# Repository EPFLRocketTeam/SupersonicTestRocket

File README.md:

# SupersonicTestRocket
Repository for the avionics going on the supersonic test rocket.
This contains the various files and folders required to get a Teensy 3.5 working with the code for data acquisition as well as the necessary post-processing scripts.

# Usage
1.  Flash the firmware onto the Teensy 3.5.  
  a. If no modifications are required to the code, this can be done by taking the file ```firmware.hex``` and flashing it directly with the Teensy flasher.  
  b. If modifications are required, Platform.io will need to be installed on the local computer on VSCode. Instructions can be found [here](https://platformio.org/platformio-ide). The required modifications can then be made and ```main.cpp``` can be recompiled using the IDE.
2.  Log data on the Teensy 3.5.  
  a. Logging should start automatically when powered on.  
  b. If it is not, press and hold button 1 for 1 second. The green LED (LED1 on the PCB) should then light up for 1 second. If the button is released during this window, logging should start indicated by the green LED staying on continuously.
3.  Stop logging on the Teensy 3.5 (optional but highly recommended!).  
  a. Logging needs to be stopped in the software using the following button sequence:  
  b. Hold button 1 for 3 seconds. The green LED should turn off and the red LED should turn on for 1 second.  
  c. Let go of all buttons for 5 seconds. After this, the red LED should turn on again for 1 second.  
  d. Hold button 2 for 7 seconds. After this, the red LED should turn on again for 1 second. Let go of the button.  
  e. Logging should now stop, indicated by no LEDs turned on. Logging can be resumed again following the instructions from step 2.  
  f. If logging is not manually stopped, there could be filesystem corruption with a power loss to the Teensy.
4.  Put the Teensy in MTP mode to transfer data to a local computer.  
  a. Flash ```mtp.ino``` onto the Teensy 3.5 using the Arduino IDE.  
  b. The SD card should appear on the computer as a normal device. transfer the most recent files.
5.  Decode the binary files using the MATLAB binary decoder.  
  a. Put the recently acquired files in the ```inFiles``` folder of the MATLAB decoder.  
  b. run the decoder ```decoder.m``` using MATLAB.  
  c. The files should now be in ```outFiles```.
6.  Run the Kalman filter on the files (not yet implemented!).  
  a. Transfer the contents of ```outFiles``` to the relevant folder of the Kalman filter.  
  b. Run the Kalman filter.  

# Contents
```
SupersonicTestRocket
|   README.md
|
│───archives            archived code
│───bin_decoder         MATLAB binary decoder for raw output files
|   |   decoder.m       the decoder itself
|   |
|   |───errorFiles      input files that had errors during processing
|   |───inFiles         input files to process by the decoder
|   |───outFiles        .csv files generated by the decoder
|   └───processedFiles  input files after successful processing
|
│───data_logger_supersonic_rocket   logger to put on the Teensy 3.5
|   |───.pio
|   |   └───build
|   |        └───teensy35
|   |           |   firmware.hex    the firmware to flash on the Teensy 3.5
|   |
|   └───src
│       │   main.cpp    the file that should be compiled with Platform.io
|
│───datasheets          datasheets for the sensors used on the rocket
│───KF                  MATLAB Kalman filter to process flight data
|   └───2D              2D simulations of the flight and KF testing
|   └───3D              the full 3D Kalman filter for flight data
|
|───mtp                 
|   └───mtp.ino         the code to run with the Arduino IDE to access the SD
|
└───PCB                 the Kicad files to reproduce the PCB
└───readings            interesting readings relevant to the project

```

# Collaborators
Joshua Cayetano-Emond

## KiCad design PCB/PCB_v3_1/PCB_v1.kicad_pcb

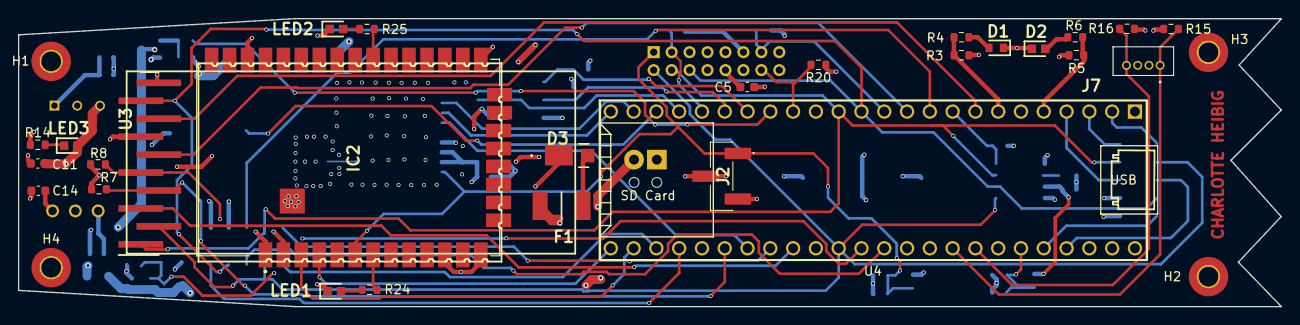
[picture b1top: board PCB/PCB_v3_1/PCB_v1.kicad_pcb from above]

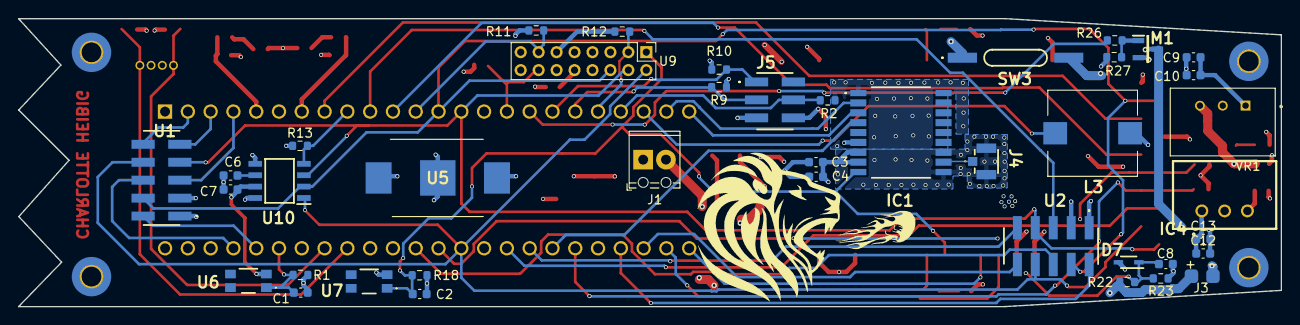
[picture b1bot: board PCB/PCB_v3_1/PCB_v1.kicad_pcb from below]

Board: 4 copper layers, 140.8 x 32.1 mm, 72 parts (41 on the bottom side), 57 nets.

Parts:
C1, C2, C3, C5, C10, C11, C13, C14: 100nF; C_0603_1608Metric
C4, C9, C12: 10uF; C_0603_1608Metric
C6: 1uF +/- 10% 10V; C_0603_1608Metric
C7: 100nF +/- 10% 10V; C_0603_1608Metric
C8: 1uF; C_0603_1608Metric
D1: White LED; LEDC1608X45N
D2: Red LED; LEDC1608X80N
D3: D_Schottky; V8PAN50M3I
D7: BZX584C3V3-G3-08; SOD2513X110N
F1: MINIASMDC150F_12-2; MINISMDC050F2
H1, H2, H3, H4: Board_Hole; MountingHole_2.2mm_M2_Pad_TopBottom
IC1: MAX-7C-0; MAX7C0
IC2: XB8X-DMUS-001; XBP9XDMRS001
IC4: TSR_0.5-2433; TSR-0.5-2433
J1: Altimax Power; TerminalBlock_Phoenix_MPT-0,5-2-2.54_1x02_P2.54mm_Horizontal
J2: 0878980304
J3: LiPo Connection; pad2
J4: CONUFL001-SMD-T; CONUFL001-SMD
J5: 57202G5203LF
J7: 1734598-4; 17345984
L3: SMI-1027-T-5V-R; SMI1027T5VR
LED1, LED2, LED3: 150060GS75000; LEDC1608X80N
M1: MNMOS; SOT95P237X112-3N
R1, R4, R6, R11, R12, R13, R20: 10kΩ; R_0603_1608Metric
R2, R9, R10, R15, R16, R18: 10k; R_0603_1608Metric
R3: 100Ω; R_0603_1608Metric
R5: 24Ω; R_0603_1608Metric
R7, R8, R27: 10kOhm; R_0603_1608Metric
R14: 10K; R_0603_1608Metric
R22, R23: ?; R_0603_1608Metric
R24, R25: 24; R_0603_1608Metric
R26: R; R_0603_1608Metric
SW3: MISM7R610
U1, U2: 57202G5205LF
U3: 1-2842102-0; HUSRSP10W50P200_2000X200X550P
U4: Teensy3.5; Teensy35_36_exterior_pins_only
U5: 3030
U6, U7: switch; RKC2SJF170SMTRLFS
U9: ADIS16470; PinHeader_2x08_P2.00mm_Vertical
U10: AIS1120SXTR; SOIC127P600X175-8N
VR1: TSR1-2450; CONV_TSR1-2450

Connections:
+3V3: C2.1, C3.1, C4.1, C5.1, C7.1, C14.1, IC1.7 (VCC_IO), IC1.8 (VCC), IC2.2 (VCC), IC4.3 (+VOUT), J5.6, R7.1, R8.1, R12.1, R13.1, R15.2, R16.2, R18.1, U1.3, U2.3, U3.7, U6.3, U9.10 (VDD), U9.11 (VDD), U9.12 (VDD), U10.7 (VDD)
+5V: C11.1, C12.1, C13.1, IC4.1 (+VIN), J7.3, LED3.2, U4.53 (Vin), VR1.3 (+VOUT)
/MISO0: U1.7, U2.7, U3.1, U4.14 (12_MISO0), U9.4 (DOUT), U10.3 (SDO)
/MOSI0: U1.4, U2.4, U3.9, U4.13 (11_MOSI0), U9.6 (DIN), U10.2 (SDI)
/RTC_supply: IC1.6 (V_BCKP), J2.2, U5.1, U5.3
/SCK0: U1.8, U2.8, U3.2, U4.40 (13_SCK0_LED), U9.2 (SCLK), U10.1 (SCL)
/aux1: J5.3, R9.2, U4.19 (27_RX1_SCK0)
/aux2: J5.1, R10.2, U4.18 (26_TX1_SCL2)
/aux3: J5.4, R2.1, U4.21 (29_PWM_CAN0TX_Touch)
/bat_voltage: C8.2, D7.1, R22.2, R23.1, U4.41 (14_A0_PWM_SCK0)
/button1: C1.1, R1.1, U4.48 (21_A7_PWM_CS0_MOSI1), U6.1
/buzzer_input: L3.1, U4.22 (30_PWM_CAN0RX_Touch)
/cs_acc: R13.2, U4.9 (7_RX3_MOSI0_SCL0), U10.4 (CS)
/cs_adis: R12.2, U4.20 (28_MOSI0), U9.3 (CS)
/cs_pressure_adc_1: U1.2, U4.49 (22_A8_PWM_Touch)
/cs_pressure_adc_2: U2.2, U4.33 (36_A17_PWM)
/cs_pressure_ee_1: U1.5, U4.4 (2_PWM)
/cs_pressure_ee_2: U2.5, U4.10 (8_TX3_MISO0_SDA0)
/cs_tc1: U1.9, U4.3 (1_TX1_MISO1_Touch)
/cs_tc2: U1.10, U4.2 (0_RX1_MOSI1_Touch)
/cs_tc3: U2.9, U4.37 (A21_DAC0)
/cs_tc4: U2.10, U4.32 (35_A16_PWM)
/dr_adis: R11.2, U4.12 (10_PWM_TX2_CS0), U9.13 (DR)
/dr_pressure_1: U1.6, U4.50 (23_A9_PWM_Touch)
/dr_pressure_2: U2.6, U4.42 (15_A1_CS0_Touch)
/enable_gnd: R26.1, U4.17 (25)
/gp0_spi: U3.3, U4.38 (A22_DAC1)
/gp3_spi: U3.8, U4.8 (6_PWM)
/gp4_spi: U3.6, U4.11 (9_PWM_RX2_CS0)
/led1: R3.2, R4.1, U4.7 (5_PWM_TX1_MISO1)
/led2: R5.1, R6.2, U4.5 (3_PWM_CAN0TX_SCL2)
/load_minus: J7.1, R15.1, U4.45 (18_A4_SDA0_Touch)
/load_plus: J7.4, R16.1, U4.46 (19_A5_SCL0_Touch)
/nReset: C2.2, IC1.9 (RESET_N), IC2.6 (~RESET), J2.1, R18.2, U7.1, U9.1 (RST)
/rx_ublox: IC1.3 (RXD), U4.24 (32_A13_TX4_SCK1)
/rx_xbee: IC2.4 (DIN/DIO14/~CONFIG), U4.30 (33_A14_TX5_CAN1TX_SCL0)
/scl_i2c: R8.2, U3.5, U4.34 (37_A18_PWM_SCL1)
/sda_i2c: R7.2, U3.4, U4.35 (38_A19_PWM_SDA1)
/sync_adis: R20.2, U4.16 (24), U9.14 (SYNC)
/timepulse_ublox: IC1.4 (TIMEPULSE), U4.36 (39_A20)
/tx_ublox: IC1.2 (TXD), U4.23 (31_A12_RX4_CS1)
/tx_xbee: IC2.3 (DIO13/DOUT), U4.31 (34_A15_RX5_CAN1RX_SDA0)
GND: C1.2, C3.2, C4.2, C5.2, C6.2, C7.2, C8.1, C9.2, C10.2, C11.2, C12.2, C13.2, C14.2, D1.1 (K), D2.1 (K), D7.2, H1.1, H2.1, H3.1, H4.1, IC1.1 (GND_1), IC1.10 (GND_2), IC1.12 (GND_3), IC2.1 (GND_1), IC2.11 (GND_2), IC2.13 (GND_3), IC2.22 (GND_4), IC2.35 (GND_5), IC2.38 (GND_6), IC4.2 (GND), J2.3, J4.2 (GND_1), J4.3 (GND_2), J5.5, J7.2, L3.2, LED1.1, LED2.1, M1.2 (S), R1.2, R2.2, R4.2, R6.1, R9.1, R10.1, R11.1, R14.2, R20.1, R23.2, R27.2, SW3.1 (A), U1.1, U2.1, U3.10, U4.1 (GND), U4.39 (GND), U5.2, U7.3, U9.7 (GND), U9.8 (GND), U9.9 (GND), U10.5 (GND), U10.8 (MP), VR1.2 (GND)
unnamed: C6.1, U10.6 (VREG)
unnamed: C9.1, C10.1, D3.1 (K), VR1.1 (+VIN)
unnamed: D1.2 (A), R3.1
unnamed: D2.2 (A), R5.2
unnamed: D3.2 (A), F1.2
unnamed: F1.1, J1.2, J3.2, R22.1
unnamed: IC1.11 (RF_IN), J4.1 (SIG)
unnamed: IC2.7 (DIO10/RSSI/PWM0), R24.1
unnamed: IC2.28 (DIO5/ASSOC), R25.2
unnamed: J1.1, J3.1, M1.1 (D), SW3.2 (B)
unnamed: LED1.2, R24.2
unnamed: LED2.2, R25.1
unnamed: LED3.1, R14.1
unnamed: M1.3 (G), R26.2, R27.1

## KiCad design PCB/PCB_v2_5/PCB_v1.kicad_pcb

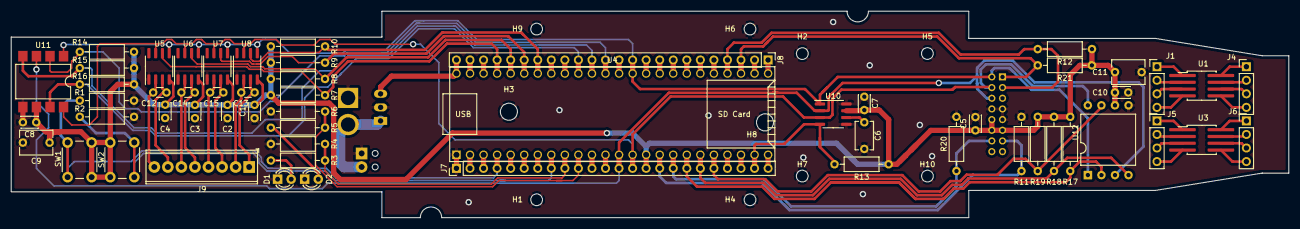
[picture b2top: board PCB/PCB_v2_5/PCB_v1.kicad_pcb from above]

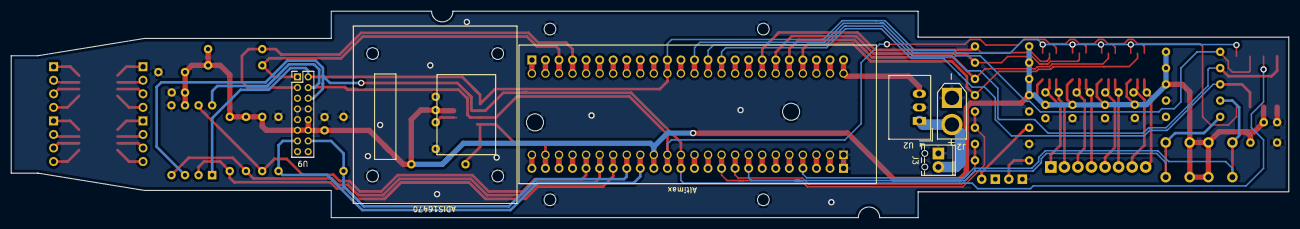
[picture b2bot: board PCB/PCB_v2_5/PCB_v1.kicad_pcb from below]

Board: 2 copper layers, 239.5 x 38.7 mm, 73 parts (6 on the bottom side), 76 nets.

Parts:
ADIS16470: ADIS16470
Altimax: AltimaxG4
C1, C2, C3, C4, C5, C8, C10: 0.1uF; C_Disc_D3.0mm_W2.0mm_P2.50mm
C6: 1uF +/- 10% 10V; C_Disc_D5.1mm_W3.2mm_P5.00mm
C7: 0.1uF +/- 10% 10V; C_Disc_D3.0mm_W2.0mm_P2.50mm
C9, C11: 10uF; C_Disc_D6.0mm_W4.4mm_P5.00mm
C12, C13, C14, C15: 10nF; C_Disc_D3.0mm_W1.6mm_P2.50mm
D1, D2: LED; LED_D3.0mm
H1, H4, H6, H9: Board_Hole; MountingHole_2.2mm_M2
H2, H5, H7, H10: IMU_hole; MountingHole_2.2mm_M2
H3, H8: Altimax_hole; MountingHole_3.2mm_M3
J1, J4, J5, J6: DIP; PinHeader_1x04_P2.54mm_Vertical
J2: XT30 Connector; AMASS_XT30U-F_1x02_P5.0mm_Vertical
J3: Altimax Power; TerminalBlock_Phoenix_MPT-0,5-2-2.54_1x02_P2.54mm_Horizontal
J7, J8: Conn_01x24_Male; PinHeader_1x24_P2.54mm_Vertical
J9: Thermocouples; TerminalBlock_Phoenix_MPT-0,5-8-2.54_1x08_P2.54mm_Horizontal
R1, R2, R4, R6, R7, R8, R9, R10, R11, R12, R13, R14, R15, R16, R17, R18, R19, R20, R21: 10kΩ; R_Axial_DIN0207_L6.3mm_D2.5mm_P10.16mm_Horizontal
R3, R5: 100Ω; R_Axial_DIN0207_L6.3mm_D2.5mm_P10.16mm_Horizontal
SW1, SW2: SW_Push; SW_PUSH_6mm
U1, U3: SOIC-8_Adapter; SOIC-8_3_to_8mm_P1.27mm
U2: TSR_1-2450; Converter_DCDC_TRACO_TSR-1_THT
U4: Teensy3.5; Teensy35_36_exterior_pins_only
U5, U6, U7, U8: MAX31855KASA; SOIC-8_3.9x4.9mm_P1.27mm
U9: ADIS16470; PinHeader_2x08_P2.00mm_Vertical
U10: AIS1120SXTR; SOIC-8_3.9x4.9mm_P1.27mm
U11: RSCMRNE015PASE3; SMDIP-8_W9.53mm
U12: RSCDJNI060PASE3; DIP-8_W13.08mm

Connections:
+3V3: C1.2, C2.2, C3.2, C4.2, C5.1, C7.1, C8.1, C9.1, C10.1, C11.1, J7.15, R7.2, R8.2, R9.2, R10.2, R12.1, R13.1, R14.2, R15.2, R16.2, R17.2, R18.2, R19.2, R21.1, SW1.2, SW2.1, U4.15, U5.4, U6.4, U7.4, U8.4, U9.10, U9.11, U9.12, U10.7, U11.6, U12.6
+5V: J8.24, U2.3, U4.53
/I/O/Button1: J7.4, R1.1, SW1.1, U4.4
/I/O/Button2: J7.8, R2.2, SW2.2, U4.8
/I/O/LED1: J7.9, R3.2, R4.1, U4.9
/I/O/LED2: J7.10, R5.1, R6.2, U4.10
/INS/CS_ADIS16470: J8.4, R12.2, U4.33, U9.3
/INS/CS_AIS1120: J7.23, R13.2, U4.23, U10.4
/INS/DR_ADIS16470: J7.16, R11.2, U4.16, U9.13
/INS/RST_ADIS16470: J8.3, R21.2, U4.32, U9.1
/INS/SYNC_ADIS16470: J7.17, R20.1, U4.17, U9.14
/MISO0: J7.14, U4.14, U5.7, U6.7, U7.7, U8.7, U9.4, U10.3, U11.8, U12.8
/MOSI0: J7.13, U4.13, U9.6, U10.2, U11.3, U12.3
/Pressure Sensors/CS_RSC015_ADC: J8.14, R15.1, U4.43, U11.4
/Pressure Sensors/CS_RSC015_EE: J8.15, R16.1, U4.44, U11.7
/Pressure Sensors/CS_RSC060_ADC: J7.19, R18.1, U4.19, U12.4
/Pressure Sensors/CS_RSC060_EE: J7.20, R19.1, U4.20, U12.7
/Pressure Sensors/DR_RSC015: J8.13, R14.1, U4.42, U11.2
/Pressure Sensors/DR_RSC060: J7.18, R17.1, U4.18, U12.2
/SCK0: J8.11, U4.40, U5.5, U6.5, U7.5, U8.5, U9.2, U10.1, U11.1, U12.1
/Thermocouples/CS_TC1: J8.21, R7.1, U4.50, U5.6
/Thermocouples/CS_TC2: J8.20, R8.1, U4.49, U6.6
/Thermocouples/CS_TC3: J8.19, R9.1, U4.48, U7.6
/Thermocouples/CS_TC4: J8.18, R10.1, U4.47, U8.6
GND: C1.1, C2.1, C3.1, C4.1, C5.2, C6.2, C7.2, C8.2, C9.2, C10.2, C11.2, D1.1, D2.1, H1.1, H2.1, H3.1, H4.1, H5.1, H6.1, H7.1, H8.1, H9.1, H10.1, J2.1, J3.1, J7.1, R1.2, R2.1, R4.2, R6.1, R11.1, R20.2, U2.2, U4.1, U5.1, U6.1, U7.1, U8.1, U9.7, U9.8, U9.9, U10.5, U10.8, U11.5, U12.5
unnamed: C6.1, U10.6
unnamed: C12.1, J9.7, U5.3
unnamed: C12.2, J9.8, U5.2
unnamed: C13.1, J9.1, U8.3
unnamed: C13.2, J9.2, U8.2
unnamed: C14.1, J9.5, U6.3
unnamed: C14.2, J9.6, U6.2
unnamed: C15.1, J9.3, U7.3
unnamed: C15.2, J9.4, U7.2
unnamed: D1.2, R3.1
unnamed: D2.2, R5.2
unnamed: J1.1, U1.1
unnamed: J1.2, U1.2
unnamed: J1.3, U1.3
unnamed: J1.4, U1.4
unnamed: J2.2, J3.2, U2.1
unnamed: J4.1, U1.8
unnamed: J4.2, U1.7
unnamed: J4.3, U1.6
unnamed: J4.4, U1.5
unnamed: J5.1, U3.1
unnamed: J5.2, U3.2
unnamed: J5.3, U3.3
unnamed: J5.4, U3.4
unnamed: J6.1, U3.8
unnamed: J6.2, U3.7
unnamed: J6.3, U3.6
unnamed: J6.4, U3.5
unnamed: J7.2, U4.2
unnamed: J7.3, U4.3
unnamed: J7.5, U4.5
unnamed: J7.6, U4.6
unnamed: J7.7, U4.7
unnamed: J7.11, U4.11
unnamed: J7.12, U4.12
unnamed: J7.21, U4.21
unnamed: J7.22, U4.22
unnamed: J7.24, U4.24
unnamed: J8.1, U4.30
unnamed: J8.2, U4.31
unnamed: J8.5, U4.34
unnamed: J8.6, U4.35
unnamed: J8.7, U4.36
unnamed: J8.8, U4.37
unnamed: J8.9, U4.38
unnamed: J8.10, U4.39
unnamed: J8.12, U4.41
unnamed: J8.16, U4.45
unnamed: J8.17, U4.46
unnamed: J8.22, U4.51
unnamed: J8.23, U4.52

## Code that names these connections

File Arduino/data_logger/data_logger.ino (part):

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
// Pins ------------------------------------------------------------------------
// I/O
const byte LED1_PIN = 7,
           LED2_PIN = 8,
           BUTTON0_PIN = 2,
           BUTTON1_PIN = 6;
// ADIS164760
const byte DR_ADIS16470_PIN = 24,
           SYNC_ADIS16470_PIN = 25,
           RST_ADIS16470_PIN = 35,
           CS_ADIS16470_PIN = 36;
// AIS1120SX
const byte CS_AIS1120SX_PIN = 31;
// Pressure sensors
const byte CS_RSC015_EE_PIN = 17,
           CS_RSC015_ADC_PIN = 16,
           DR_RSC015 = 15;
const byte CS_RSC060_EE_PIN = 28,
           CS_RSC060_ADC_PIN = 27,
           DR_RSC060 = 26;
// Thermocouples
const byte CS_TC1 = 23,
           CS_TC2 = 22,
           CS_TC3 = 21,
           CS_TC4 = 20;


// Atmosphere ------------------------------------------------------------------
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
// ADIS16470 IMU ---------------------------------------------------------------
// Call ADIS16470 Class
ADIS16470 IMU(CS_ADIS16470_PIN, DR_ADIS16470_PIN, RST_ADIS16470_PIN);
uint8_t *IMUburstData; // Temporary Data Array

// AIS1120SX Accelerometer -----------------------------------------------------
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
  // Start logging
  Serial.println("Logging started. Press the button to stop.");
  digitalWrite(LED1_PIN, LOW);
  digitalWrite(LED2_PIN, HIGH);
  // LOGGING LOOP
  // Log data until button pressed or file full.
  while (logFlag) {
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    // I/O
    // read the state of the buttons
    indiv_button_state[0] = digitalRead(BUTTON0_PIN);
    indiv_button_state[1] = digitalRead(BUTTON1_PIN);
    getButtonArrayState();

    // If the state changed, due to noise or pressing:
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          + IO_MARGIN && logFlag == 1) {
        Serial.println("First check to stop logging passed.");
        logFlag = 2;
        digitalWrite(LED1_PIN, LOW);
      } else if (button_lastState == LOG_OFF_SEQ2_STATE \
                 && button_stateTime[LOG_OFF_SEQ2_STATE] >= LOG_OFF_SEQ2_DURATION \
                 && button_stateTime[LOG_OFF_SEQ2_STATE] <= LOG_OFF_SEQ2_DURATION \
                 + IO_MARGIN && logFlag == 2) {
        Serial.println("Second check to stop logging passed.");
        logFlag = 3;
        digitalWrite(LED1_PIN, HIGH);
      } else if (button_lastState == LOG_OFF_SEQ3_STATE \
                 && button_stateTime[LOG_OFF_SEQ3_STATE] >= LOG_OFF_SEQ3_DURATION \
                 && button_stateTime[LOG_OFF_SEQ3_STATE] <= LOG_OFF_SEQ3_DURATION \
                 + IO_MARGIN && logFlag == 3) {
        Serial.println("Third check to stop logging passed. Stopping Logging");
        logFlag = 0;
        digitalWrite(LED1_PIN, LOW);
      } else {
        Serial.println("Check failed. Logging will continue as normal.");
        digitalWrite(LED2_PIN, HIGH);
        logFlag = 1;
      }
    } else {
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          && button_stateTime[LOG_OFF_SEQ1_STATE] >= LOG_OFF_SEQ1_DURATION \
          && button_stateTime[LOG_OFF_SEQ1_STATE] <= LOG_OFF_SEQ1_DURATION \
          + IO_MARGIN && logFlag == 1) {
        digitalWrite(LED1_PIN, HIGH);
        Serial.println("Inside window for first check.");
      } else if (button_state == LOG_OFF_SEQ2_STATE \
                 && button_stateTime[LOG_OFF_SEQ2_STATE] >= LOG_OFF_SEQ2_DURATION \
                 && button_stateTime[LOG_OFF_SEQ2_STATE] <= LOG_OFF_SEQ2_DURATION \
                 + IO_MARGIN && logFlag == 2) {
        digitalWrite(LED1_PIN, HIGH);
        Serial.println("Inside window for second check.");
      } else if (button_state == LOG_OFF_SEQ3_STATE \
                 && button_stateTime[LOG_OFF_SEQ3_STATE] >= LOG_OFF_SEQ3_DURATION \
                 && button_stateTime[LOG_OFF_SEQ3_STATE] <= LOG_OFF_SEQ3_DURATION \
                 + IO_MARGIN && logFlag == 3) {
        digitalWrite(LED1_PIN, HIGH);
        Serial.println("Inside window for third check.");
      } else {
        digitalWrite(LED1_PIN, LOW);
        digitalWrite(LED2_PIN, HIGH);
      }
    }
    button_lastState = button_state;
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  loggingFile.truncate();
  loggingFile.rewind();
  loggingFile.close();
  digitalWrite(LED2_PIN, LOW);

}

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  delay(1000);

  // Set up I/O
  pinMode(LED1_PIN, OUTPUT);
  pinMode(LED2_PIN, OUTPUT);
  pinMode(BUTTON0_PIN, INPUT);
  pinMode(BUTTON1_PIN, INPUT);
  Serial.println("I/O has been set up");


  digitalWrite(LED1_PIN, LOW);
  digitalWrite(LED2_PIN, HIGH);
  delay(500);
  digitalWrite(LED2_PIN, LOW);
  delay(5000);

  // Set up the ADIS16470
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  // I/O
  // read the state of the buttons
  indiv_button_state[0] = digitalRead(BUTTON0_PIN);
  indiv_button_state[1] = digitalRead(BUTTON1_PIN);
  getButtonArrayState();

  // If the state changed, due to noise or pressing:
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    if (button_lastState == LOG_ON_STATE \
        && button_stateTime[LOG_ON_STATE] >= LOG_ON_DURATION \
        && button_stateTime[LOG_ON_STATE] <= LOG_ON_DURATION + IO_MARGIN) {
      digitalWrite(LED1_PIN, LOW);
      Serial.println("Logging will start.");
      logData();
      Serial.println("Logging stopped.");
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    if (button_state == LOG_ON_STATE \
        && button_stateTime[LOG_ON_STATE] >= LOG_ON_DURATION \
        && button_stateTime[LOG_ON_STATE] <= LOG_ON_DURATION + IO_MARGIN) {
      digitalWrite(LED1_PIN, HIGH);
      Serial.println("Inside 1 to 2 sec window");
    } else {
      digitalWrite(LED1_PIN, LOW);
    }
  }
  button_lastState = button_state;
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
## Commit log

2021-04-06 transferred code from the previous (private) repository
2021-04-06 started main data logger
2021-04-08 added sdfat file setup using a rolling counter
2021-04-09 added logging loop properly. data logging on SD *should* now work
2021-04-12 added some datasheets and readings
2021-04-19 added new datasheets
2021-04-20 added buttons and event to start/stop logging
2021-04-21 created platformio files
2021-04-21 transferred button functions into separate file
2021-04-21 fixed a few bugs when switching states
2021-04-22 some cleanup for button functions
2021-04-22 setup data acquisition with separate tasks for each sensor
2021-04-22 add beat skip checking
2021-04-23 defined packet types and started decoding function
2021-04-23 matlab decoder
2021-04-24 created i/o file. setup libraries for sensors and added boot checks
    also did a bit of housecleaning for the file structure
2021-04-25 ADIS16470 data acquisition done
2021-04-26 added TC and RSC. started sensor and wrapper classes
2021-04-26 setup the ADIS16470 wrapper
2021-04-26 wrappers bug fixes
2021-04-26 RSC wrapper
2021-04-28 wrappers almost done. debugging now
2021-04-29 Added MTP, fixed a few bugs and wrote the readme
2021-04-30 started unit testing and reorganized libraries
2021-04-30 button tests half written
2021-04-30 finished button testing
2021-05-02 added PCB and testing for the AIS library
2021-05-07 added the decoders for the other sensors
    and made logging start automatically
2021-05-20 testing new file
2021-05-20 removing test file
2021-05-20 typos with spacing in readme
2021-05-22 rearrange file structure that was bugged because of different case in names
2021-05-22 updated gitignore
2021-05-22 removed workspace
2021-05-23 fixed issues for the MAX and ADIS sensors
2021-05-24 added sampling frequency selection for RSC wrapper
2021-05-31 adjusting wrappers for changes done to the libraries
2021-06-02 made DR lines interrupt-driven
2021-06-02 moved volatible variables outside of the classes since it wasn't working great
2021-06-06 fixed indenting and added mkdir for the necessary folders
2021-06-10 added detachInterrupts and changed acquisition frequencies
2021-06-13 added data from the first flight
2021-06-14 cleanup from old interrupts and bug in decoder
2021-06-19 added altimax interrupt and fixing some timing issues
2021-06-27 code for SFT
2021-07-11 started working on a nicer serial console output
2021-07-12 preparing rest of code to work with GS
    mainly fixed the wrappers and the packets that they called
2021-07-12 created first text console
    testing still needs to be done
2021-07-15 preliminary debugging for the serial console
2021-07-16 serial packet values now have fixed size arrays
    TODO: change this to work with pointers properly
2021-07-17 formatting and cleaning up packets
2021-07-17 added invalid measurement error+mach/airspeed readings
2021-07-18 created flowCalculations file
2021-07-18 changed packets to all use floats for simplicity in decoding and using the serial monitor
2021-07-18 started python serial monitor and decoder
2021-07-19 created packet decoder
    Also created a PacketType dataclass that contains the required information for the decoding
2021-07-19 created file manager to read binary files in python
2021-07-21 add datasheets of eggtimer components
2021-07-27 started dashboard and files now moved after decoding
2021-07-27 fixed altitude calculation and inactive sensors no longer send serial data
2021-07-31 code for error checking and red light for bug in ADIS
2021-08-01 improved serial output and added error latching
    still some bugs to fix. namely, text decoration doesn't work properly
2021-09-04 plotFlight module
2021-10-17 added 3d plotter and logs from Cernier
2021-10-17 added Cernier data for real
2021-10-29 Renaming .h to .hpp Creating Packer class to harmonize packet management
2021-10-29 .h to .hpp and Packet (part2)
2021-11-03 create new branch and cleanup folder structure
2021-11-03 created drag work analysis script
2021-11-04 thrust curve analysis
2021-11-12 Implemented packets for all wrappers (Remain Altimax wrapper to do)
2021-11-12 Rework of setup: Use virtual class Sensor to streamline setup
2021-11-12 Added missing ; Started adapting `acquireData`
2021-11-12 Moved NUM_SENSORS to be a global variable
2021-11-12 Use pointers to return packets
2021-11-12 Compilable new dataAcquisition (Use virtual Packet and Sensor) Removed calls to "serialOutput" (may need rework since virtual inputs)
2021-11-12 added Schlieren pdf and blowdown tunnel simulator
2021-11-20 setup documentation
2021-11-20 implemented altimax wrapper
2021-11-20 removed yml file to be able to push
2021-11-20 deleted workflows folder to push
2021-12-17 added contact force calculation
2022-01-04 started routing
2022-01-04 Started PCB v1.5
    - Added diode to schematic to stop Altimax from beeping when USB powered
    - Reduced PCB size to fit in 100x40mm
    - Changed some pins on the Teensy and started routing
2022-02-07 Commit Doxygen
2022-02-08 Documented CustomTypes.hpp
2022-02-08 Documented Sensor class Updated `errors` storage
2022-02-08 Removed Doc from git (for now)
2022-02-08 Removed MAN doc
2022-02-08 Style corrections for Doxygen
2022-02-08 Added doc to ADIS
2022-02-08 Put HTML doc back on Git README.md style corrected Doxygen parameters adpated (MathJax for pretty math in HTML)
2022-02-09 Shortened names
2022-02-09 Added comments to doc
2022-02-09 isMeasurementInvalid is now pure virtual decodeErrorCode now needs to be provided with errorArray to be filled
2022-02-09 Added interface for Serial printing of packets
2022-02-09 Added Printable body for ADIS Removed DR_PIN since unused
2022-02-09 Added getPrintableContent for the other sensors
2022-02-11 Added header to store useful macros (for now, 'unused(var)' macro)
2022-02-11 Doc correction, some style change
2022-02-11 More doc correction
2022-02-11 Added doc, some style change
2022-02-11 Hardcoded the length for ADIS16470 wordBurst()
2022-02-11 Corrected typo
2022-02-11 Added 'lastPackets' to store pointers to the two types of packets (pressure and temperature) Partial documentation; to be completed after review of the actual sensor driver
2022-02-11 Doc for MAX31855
2022-02-11 Documented IO
2022-02-12 Cleaned up the doc
2022-02-12 added datasheets
2022-02-12 added custom library symbols
2022-02-12 deleted documentation
    Documentation was already added by @spacewolfXfr in recent commits, so this older version of documentation has been deleted in case there are any conflicts and to avoid any confusion. There might be 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
2022-02-14 Added units
2022-02-14 Provided default (max) values to `CHECK_INTEVAL` and `MEAS_INTERVAL`
2022-02-15 added flight data
2022-02-15 updated flight comparison files
2022-02-15 added pitot data to comparison
2022-02-22 Removed dueByTime to avoid packet type confusion
2022-02-22 Removed old serialOutput
2022-02-22 Moved error encoding/decoding to Packet.hpp
2022-02-22 Size correction for Serial printing
2022-02-22 Moved Sensors to src
2022-02-23 Removed unused C++ headers
2022-02-23 Get rid of destructor declaration
2022-02-25 first version of the avionics code
2022-02-25 fixed issues with SD card logging
2022-02-25 data analysis script in python and first KF
2022-02-26 refactored code and did minor memory optimizations
    commented and reformatted the code to be a bit cleaner.
    still missing the recovery section to reformat
2022-02-27 added openrocket folder and first file
2022-02-27 changed timestep to match the actual value
2022-02-27 bug fixes
    moved some variables to be global
    put beeps back in milliseconds
2022-03-01 added results from the 2nd day of drop tests
    also changed file nomenclature and added folders
2022-03-03 Switched to DEBUG mode New serial printing
2022-03-04 Cheap&Dirty live packet display
2022-03-04 Debug
2022-03-04 RM some personnal files
2022-03-08 Should fix flickering
2022-03-13 added OR v3
    and renamed v2
2022-03-14 added motors
2022-03-15 Added Wrapper for MAX7
2022-03-16 added OR v4
2022-03-18 wire harness v1
2022-03-19 Added ground station
2022-03-19 Added MAX7 and begining of XBee
2022-03-19 Trying to add full dir
2022-03-19 Copy of ground station commited
2022-03-19 Renamed to original name
2022-03-19 created simplified diagram
    ribbons now only have 1 cable if all the interior cables go between the same boards
2022-03-19 added load cell
2022-03-19 Corrected MAX7
2022-03-19 Split set destination for setup and during exec
2022-03-19 Added GNSS Library to platformIO deps
2022-03-19 Commented out custom debug tools
2022-03-19 Re removed debug lib
2022-03-19 started first version of load cell wrapper
    still doesn't work. a few things to figure out regarding packet reading
2022-03-20 Added `send` function for XBee Wrapper Add MACRO function to ensure big-endian writing Add big-endian support for all packets Separate body description of each packet for easy ext import
2022-03-20 What the last commit should have contained
2022-03-20 Bug correction, import from GS only needed file
2022-03-22 Added XBee in main loop
2022-03-22 More adaptation in main
2022-03-22 Removed SerialMonitor
2022-03-22 Updated link from GS to data_logger sensors
2022-03-22 Moved Hermes packets body into specific folder (Help for import from GS)
2022-03-23 HERMES packets implemented on the GS
2022-03-23 enabled logging of received packets
2022-03-25 Debug + update PCB
2022-03-25 Use generic `Stream` instead of `SoftwareSerial` (Pass them by ref)
2022-03-26 Adapted data decoding (do not double check packetType VS packetSize)
2022-03-26 Changed back printing
2022-03-26 Corrected setup for XB8X
2022-03-26 Set analog read consts
2022-03-26 Updated AD8556 Wrapper Update PCB
2022-03-26 Added AD8556Wrapper
2022-03-26 Added Debug library
2022-03-26 Added AD8556 in data analysis
2022-04-30 Made README for `data_logger`
2022-04-30 added AD8556 packet
2022-04-30 renamed directory
2022-05-04 Corrected docstring
2022-05-04 Changed display to include clock (in ms)
2022-05-04 Correctde number of sensors
2022-05-04 Added AD8556 packets
2022-05-04 Removed dead code
2022-05-05 Update absolute symlink to relative symlink
2022-05-05 Massive changes everywhere
2022-05-05 Repqired symlink
2022-05-10 Now return error on unsuccessful setup
2022-05-10 Corrected Packet ID for load cell
2022-05-10 Added experiment duration constant
2022-05-10 Typo correction + Started improving plotting (Streamlining)
2022-05-10 Style change
2022-05-12 Fixed reading type
2022-05-12 Fixed baud rate for radio
2022-05-12 Removed debug messages
2022-05-12 Removed debug messages and enabled radio
2022-05-12 Fixed BIG_ENDIAN macro
2022-05-13 Changed GPS library; GPS OK
2022-05-13 Adjusted radio; radio emissions ~OK
2022-05-13 Push AIS doc
2022-05-13 HERMES 2 ready to fligh with Brique Sensors ready: - GPS - ADIS - TC1 - RSC
2022-05-30 added hermesAVsim executable
2022-06-10 removed unused executables
2022-06-10 added hermesRelay directory
2022-06-13 Added dummy data and datasheets
